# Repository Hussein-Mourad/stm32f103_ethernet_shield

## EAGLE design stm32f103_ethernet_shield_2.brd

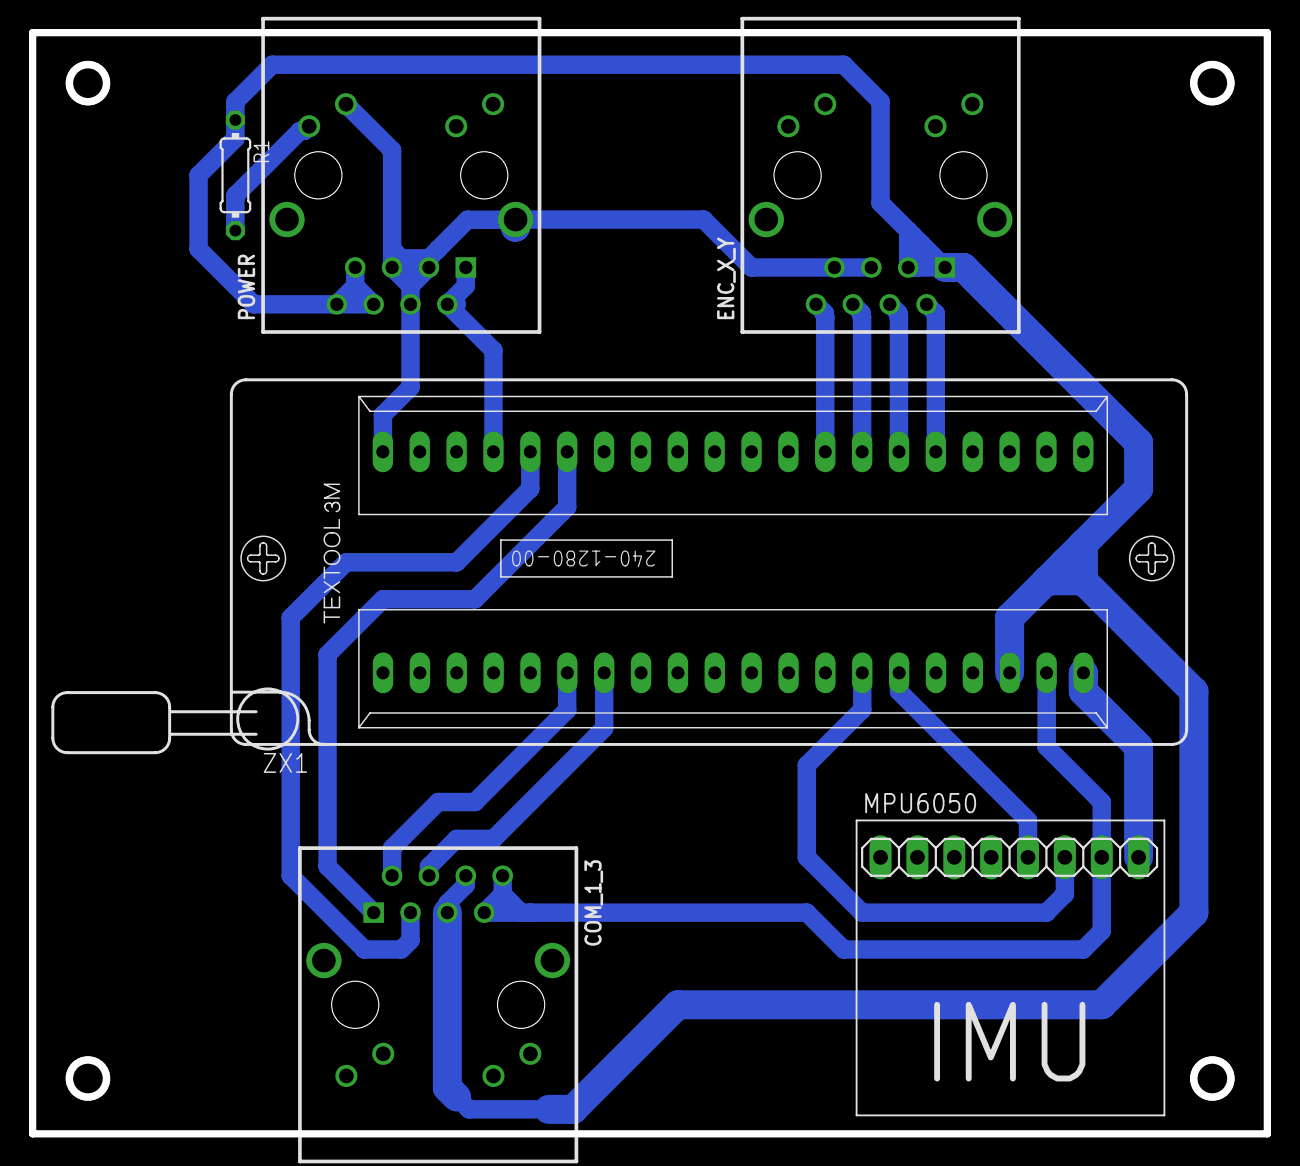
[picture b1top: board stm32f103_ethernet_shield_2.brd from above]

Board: 2 copper layers, 85.1 x 75.9 mm, 6 parts (0 on the bottom side), 16 nets.

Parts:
COM_1_3: RJ45; J0-A/B/F
ENC_X_Y: RJ45; J0-A/B/F
MPU6050: IMU_ROBOCON_GY521; IMU_GY521
POWER: RJ45; J0-A/B/F
R1: 150R; 0204/7
ZX1: ZIF_401280; 240-1280-00-0602J

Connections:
3V3@1: MPU6050.VCC, ZX1.20
5V: COM_1_3.5, COM_1_3.6, ENC_X_Y.1, ENC_X_Y.3, POWER.6, POWER.7, POWER.8, R1.1, ZX1.18
GND@1: COM_1_3.7, COM_1_3.8, MPU6050.GND, ZX1.19
GND@3: ENC_X_Y.5, ENC_X_Y.7, POWER.3, POWER.4, POWER.5, POWER.11, POWER.S2, ZX1.40
PA_0: ENC_X_Y.2, ZX1.25
PA_1: ENC_X_Y.4, ZX1.26
PA_2: ENC_X_Y.6, ZX1.27
PA_3: ENC_X_Y.8, ZX1.28
PA_9: COM_1_3.2, ZX1.6
PA_10: COM_1_3.4, ZX1.7
PB_6: MPU6050.SCL, ZX1.14
PB_7: MPU6050.SDA, ZX1.15
PB_10: COM_1_3.1, ZX1.35
PB_11: COM_1_3.3, ZX1.36
RA1: POWER.12, R1.2
RESET: POWER.1, POWER.2, ZX1.37

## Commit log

2022-02-06 init
2022-02-08 Added a board design
2022-02-08 Added a second design
2022-02-08 Removed old design
2022-02-08 Removed old backups
2022-02-11 backup
